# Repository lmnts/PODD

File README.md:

# Post Occupancy Data Device

*A tool to understand how buildings perform in terms of occupant comfort.*

*&nbsp;&nbsp;&nbsp;&nbsp;https://lmnarchitects.com/tech-studio/*

The Post Occupancy Data Device (PODD) is a small, networked, multi-sensor device that:

  * addresses the need for more granular data on buildings once they have been occupied
  * offers a lower cost, less precious alternative to standard building enviornmental sensors
  * gives building designers greater control over the tools available to them to understand their buildings
 
PODD is under active development and should be thought of as early alpha quality for both the software and hardware.

- [Features](#features)
- [Hardware](#hardware)
  - [Operational Hardware](#operational-hardware)
  - [Sensors](#sensors)
- [Building](#building)
  - [Hardware Setup](#hardware-setup)
  - [Software Setup](#software-setup)
- [Data Access](#data-access)
- [Known Issues](#known-issues)
- [License](#license)
- [Reporting Issues](#reporting-issues)
- [Contact](#contact)

## Features

The PODD is our solution to the gap in the available post-occupancy evaluation tools. The units are designed to be networked together in large numbers, storing and uploading data from seven sensors that have been identified as most relevant for occupant comfort in buildings.

Each unit has the following features:

  * Air quality sensors: particulate matter (PM2.5 and PM10), CO<sub>2</sub>, CO
  * Thermal comfort sensors: combined temperature and humidity sensor, radiant temperature
  * Illuminance sensor
  * Sound level sensor
  * On board data storage: micro SD card
  * Real Time Clock (RTC)
  * Wireless communication using 802.15.4 standard (900 MHz)
  * Onboard Ethernet 
  * Power via battery, USB, or PoE
  * Current cost: ~$400 (note: the CO and CO<sub>2</sub> sensors together are 1/4 of the cost and the production cost for the board is currently in the small-batch range)

## Hardware

Details can be found in [Hardware](Hardware).

The PODD is designed to be a self-powered unit that can communicate with other units as well as transmit information over ethernet. The portable battery currently used is the primary source of power. All other power sources provide power by charging the battery. Depending on sample rates, the units can run on battery power for up to 8 days.

### Operational Hardware

The current version of PODD uses the following components to run:

  * Teensy++ 2.0
  * MicroSD Reader 
  * DS3234 Real Time Clock
  * Ethernet Module (for server or other remote communication)
  * PoE module
  * XBee 900 Mesh Kit
  * Rechargeable USB battery
  * Various supporting components (resistors, capacitors, op-amps, etc.)

### Sensors

The current version of PODD uses the following sensors:

  * Sensirion SPS30: particulate matter
  * COZIR-A: CO<sub>2</sub>
  * SPEC Sensor 3SP_CO_1000: CO
  * Honeywell HIH8120-021: dry bulb temperature and humidity
  * PR222J2: radiant temperature
  * OPT3001: illuminance
  * CMR-2747PB-A: sound level

## Building

### Hardware Setup

The PODD can be built entirely on a breadboard for initial prototyping and testing. All parts can be obtained in a DIP package for breadboarding or soldering to a perf-board. For use with the PCB design included, you will need to obtain the supporting components in their SMD packages. The gerber files in the Hardware folder can be used for making the PCB or having it manufactured.

A full list of parts can be found in [this spreadsheet](Hardware/PODD_v1.2_PartsList.xlsx).

To assemble the PODD, see [this assembly document](Hardware/PODD_v1.2_Assembly.pdf).  This document also describes issues with various sensors and other components, and how to operate the sensors.

### Software Setup

You will need the following:

  * [Arduino IDE](https://www.arduino.cc/en/Main/Software)
  * [Teensy add-ons](https://www.pjrc.com/teensy/td_download.html)
  * The sensor and component-specific libraries included in [Libraries](Software/Libraries)

After installing the Arduino IDE and the Teensy add-ons, follow the instructions to [install Arduino Libraries](https://www.arduino.cc/en/Guide/Libraries).

Once the above software is installed, the PODD firmware in [SensorPod_FW](Software/Sketches/SensorPod_FW) can be uploaded to the PODD.  The firmware provides an interactive menu which can be accessed through a serial interface such as provided by the Arduino IDE.  The interactive menu can only be accessed during the PODD startup sequence -- once the PODD enters data-taking mode, it will no longer respond to serial input.

## Data Access
_work in progress_

The PODD collects data from all the sensors at the specified sample rates and logs those to the on-board SD card in the form of a CSV file. All settings are also stored on the SD card as a separate CSV file. If any unit is designated as a controller and connected to Ethernet, the data from all the units on the same network will be uploaded to a server specified by the user.

## Known Issues
_work in progress_

1. Most portable USB power banks automatically shut off to save power whenever the current draw is low: as the PODD draws a much smaller amount of power than the cell phones these power banks are designed to charge, these batteries will often not provide continuous power to a PODD and cannot be used.  The TalentCell batteries we use do not have this feature, but also cannot be recharged via USB/PoE as intended in the current PCB design.
1. R11, which is part of the battery charging circuit, should be 390 Ohms.  The PCB design called for a larger (too large) resistor.
1. The CO sensor output is uncalibrated and we are as yet unsure how to quantify the results.  The C and R pins many be reversed on this sensor's PCB headers.
1. The sound sensor currently provides time-averaged sound levels in an arbitrary linear unit, rather than the logarithmic decibel (dB) scale.  Conversion to dB(Z) is being investigated, but the frequency-weighted dB(A) or dB(C) more commonly used for human hearing may require processing capabilities beyond that provided by the current hardware.

## License

**PODD hardware is released under [Creative Commons Share-alike Non-Commercial 4.0 International](https://creativecommons.org/licenses/by-nc-sa/4.0/).**

**PODD code, firmware, and software is released under the [GNU Affero General Public License](https://www.gnu.org/licenses/).**

See the full text files for details on both licenses.

Our open source goals include 1) sharing new ways to understand buildings with the AEC industry and 2) engaging with a larger group of practitioners and researchers to develop new tools for the AEC industry.

## Reporting Issues

You can open a ticket on [GitHub](https://github.com/lmnts/PODD/issues).

## Contact

Contact pmilusheva@lmnarchitects.com or csavage@lmnarchitects.com with any questions or comments.

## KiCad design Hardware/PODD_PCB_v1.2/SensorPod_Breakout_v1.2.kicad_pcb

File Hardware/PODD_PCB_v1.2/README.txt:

# Assembly

## Teensy++ 2.0 Modifications

The Teensy++ 2.0 is used in 3.3V mode in order to save power. Before plugging the teensy in, please do the following:

# Using these files

The files in this repo are for the LMN SensorPod Phase 1 hardware. To open them, you'll need KiCAD:

- http://kicad-pcb.org/

It may also be helpful to use these libraries:

- https://github.com/mogar/KiCAD_libs

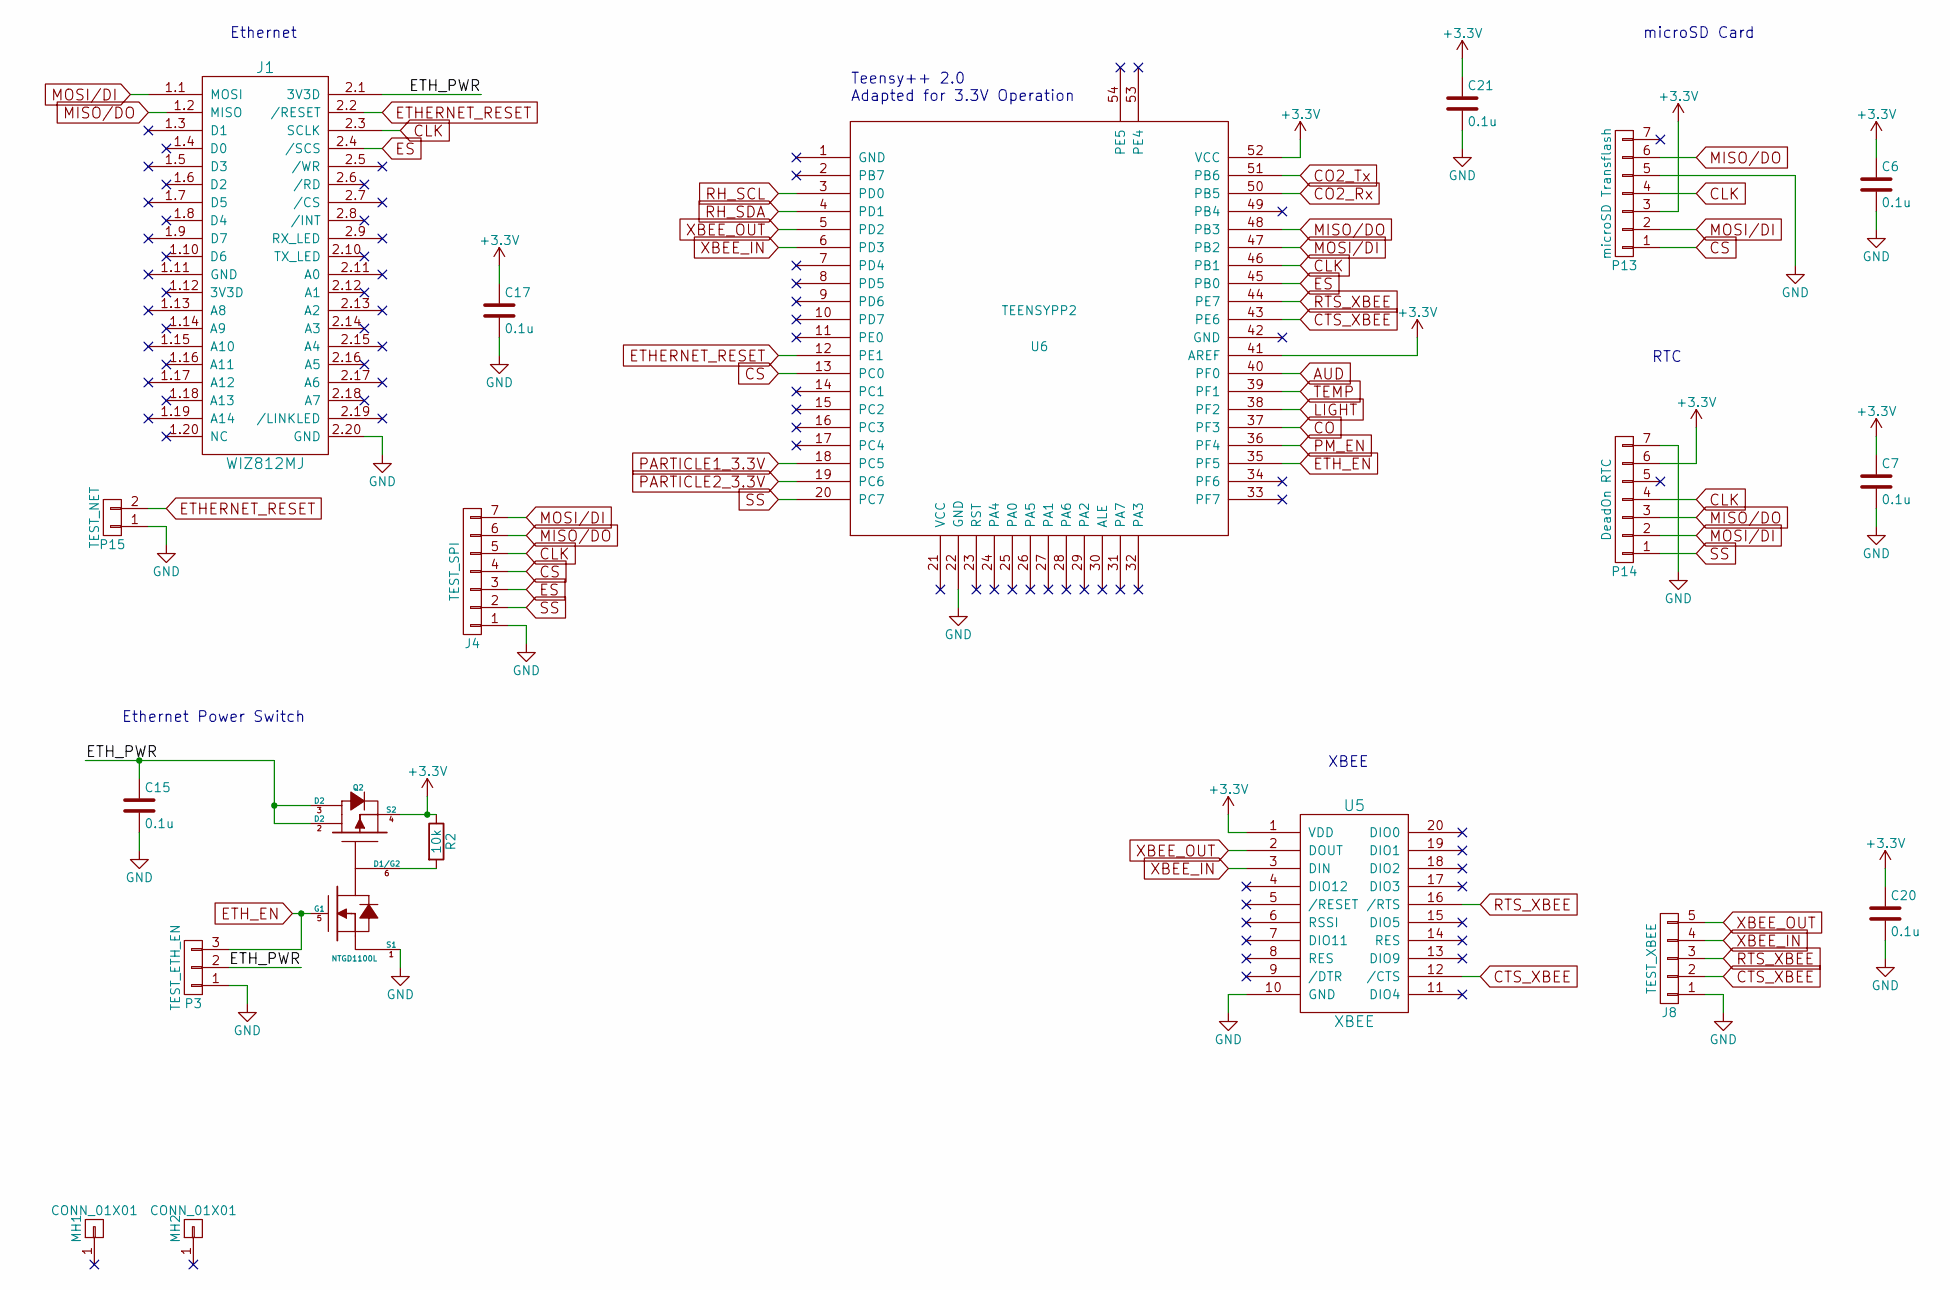
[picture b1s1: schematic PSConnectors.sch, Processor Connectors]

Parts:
C6, C7, C15, C17, C20, C21: 0.1u; C_0805
J1: WIZ812MJ
J4: TEST_SPI; Pin_Header_Straight_1x07_Pitch2.54mm
J8: TEST_XBEE; Pin_Header_Straight_1x05_Pitch2.54mm
MH1, MH2: CONN_01X01; MountingHole_3.2mm_M3
P3: TEST_ETH_EN; Pin_Header_Straight_1x03_Pitch2.54mm
P13: microSD Transflash; SD_Card
P14: DeadOn RTC; DeadOn_RTC
P15: TEST_NET; Pin_Header_Straight_1x02_Pitch2.54mm
Q2: NTGD1100L; TSOT-23-6_HandSoldering
R2: 10k; R_0805
U5: XBEE
U6: TEENSYPP2

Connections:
+3V3: C6.1, C7.1, C17.1, C20.1, C21.1, P13.3, P14.6, Q2.4 (S2), R2.1, U5.1 (VDD), U6.41 (AREF), U6.52 (VCC); also elsewhere on the board
/Processor Connectors/ETH_PWR: C15.1, J1.2.1 (3V3D), P3.2, Q2.2 (D2), Q2.3 (D2)
AUD: U6.40 (PF0); also elsewhere on the board
CLK: J1.2.3 (SCLK), J4.5, P13.4, P14.4, U6.46 (PB1)
CO: U6.37 (PF3); also elsewhere on the board
CO2_Rx: U6.50 (PB5); also elsewhere on the board
CO2_Tx: U6.51 (PB6); also elsewhere on the board
CS: J4.4, P13.1, U6.13 (PC0)
CTS_XBEE: J8.2, U5.12 (/CTS), U6.43 (PE6)
ES: J1.2.4 (/SCS), J4.3, U6.45 (PB0)
ETHERNET_RESET: J1.2.2 (/RESET), P15.2, U6.12 (PE1)
ETH_EN: P3.3, Q2.5 (G1), U6.35 (PF5)
GND: C6.2, C7.2, C15.2, C17.2, C20.2, C21.2, J1.2.20 (GND), J4.1, J8.1, P3.1, P13.5, P14.7, P15.1, Q2.1 (S1), U5.10 (GND), U6.22 (GND); also elsewhere on the board
LIGHT: U6.38 (PF2); also elsewhere on the board
MISO/DO: J1.1.2 (MISO), J4.6, P13.6, P14.3, U6.48 (PB3)
MOSI/DI: J1.1.1 (MOSI), J4.7, P13.2, P14.2, U6.47 (PB2)
unnamed: Q2.6 (D1/G2), R2.2
PARTICLE1_3.3V: U6.18 (PC5); also elsewhere on the board
PARTICLE2_3.3V: U6.19 (PC6); also elsewhere on the board
PM_EN: U6.36 (PF4); also elsewhere on the board
RH_SCL: U6.3 (PD0); also elsewhere on the board
RH_SDA: U6.4 (PD1); also elsewhere on the board
RTS_XBEE: J8.3, U5.16 (/RTS), U6.44 (PE7)
SS: J4.2, P14.1, U6.20 (PC7)
TEMP: U6.39 (PF1); also elsewhere on the board
XBEE_IN: J8.4, U5.3 (DIN), U6.6 (PD3)
XBEE_OUT: J8.5, U5.2 (DOUT), U6.5 (PD2)

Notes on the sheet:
RTC
microSD Card
Ethernet
XBEE
Teensy++ 2.0 Adapted for 3.3V Operation
Ethernet Power Switch

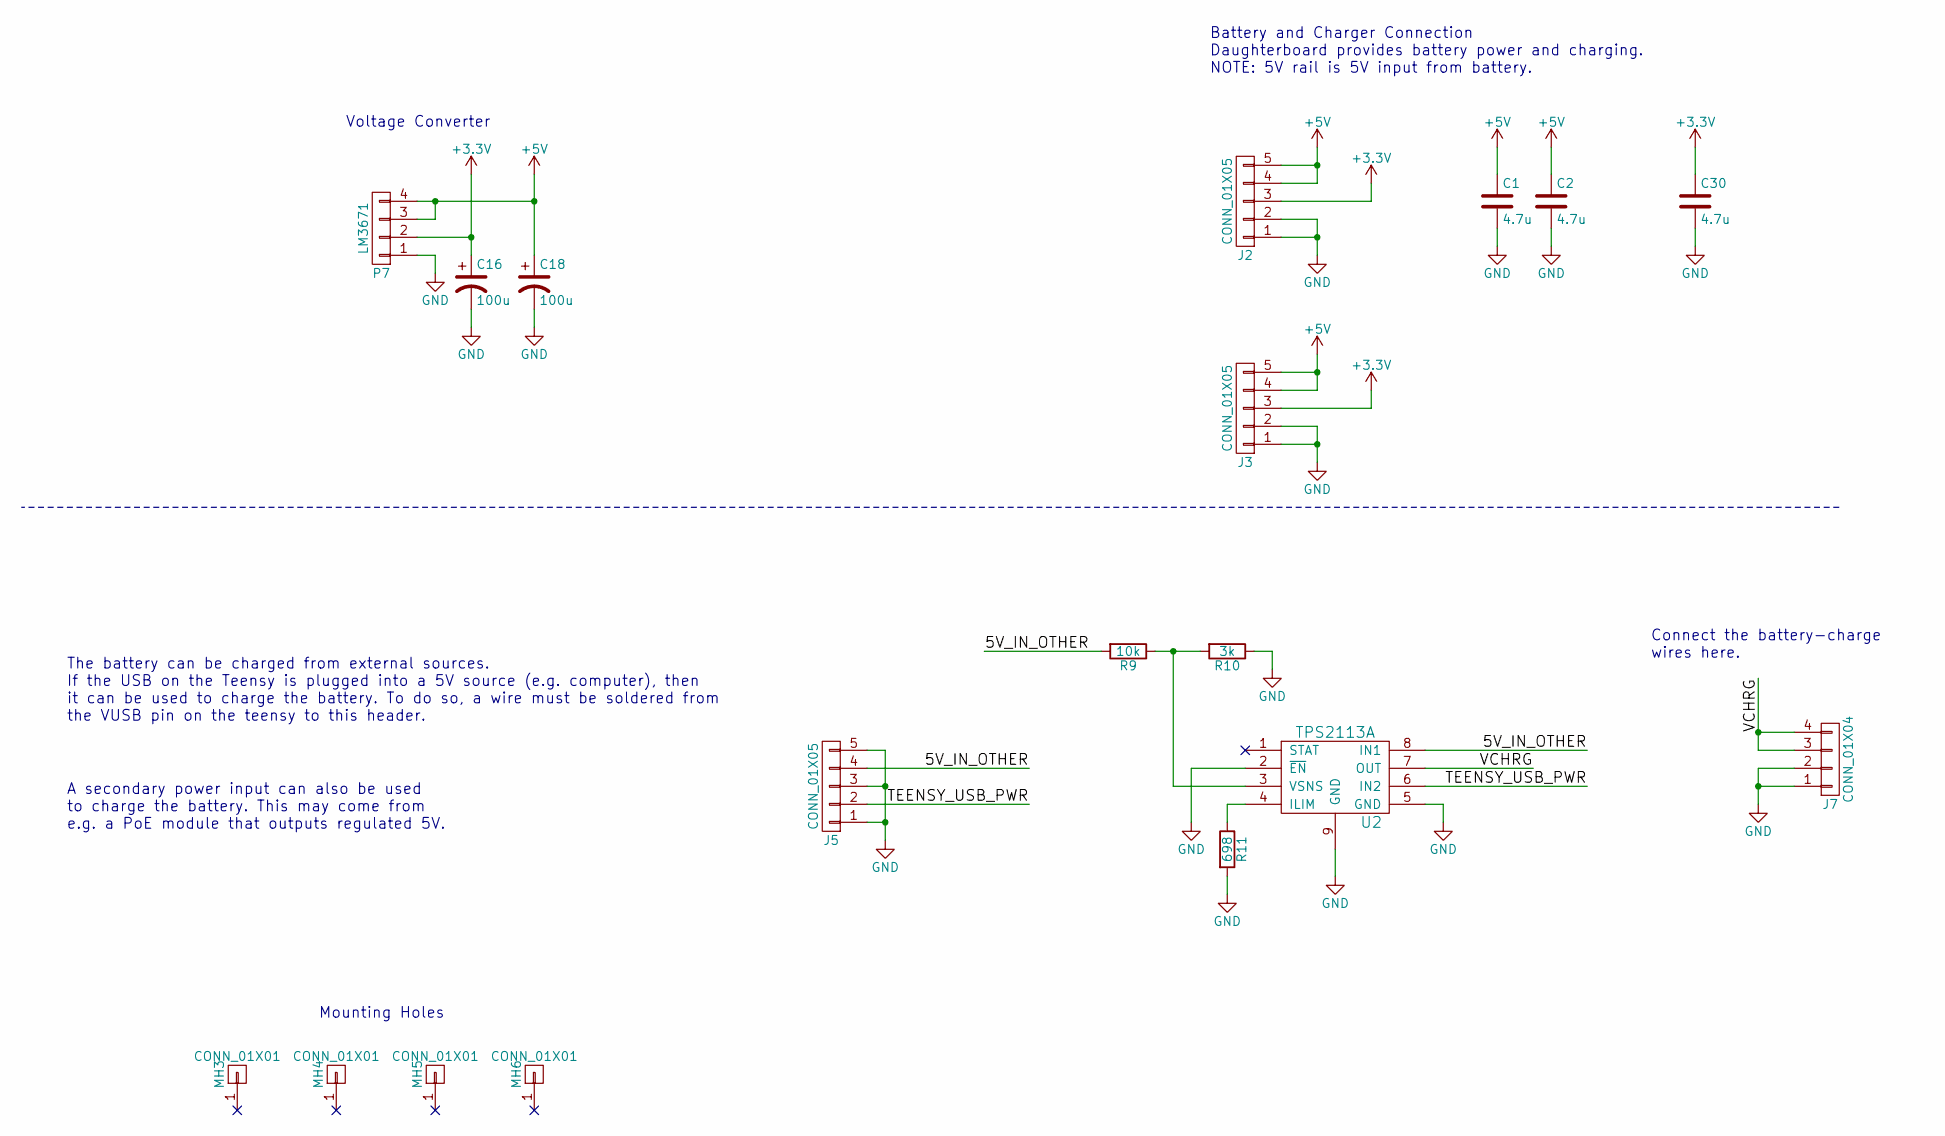
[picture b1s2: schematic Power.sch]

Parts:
C1, C2, C30: 4.7u; C_0805
C16, C18: 100u; CP_Radial_D5.0mm_P2.00mm
J2, J3: CONN_01X05; Pin_Header_Straight_1x05
J5: CONN_01X05; Pin_Header_Straight_1x05_Pitch2.54mm
J7: CONN_01X04; Pin_Header_Straight_1x04_Pitch2.54mm
MH3, MH4, MH5, MH6: CONN_01X01; MountingHole_3.2mm_M3
P7: LM3671
R9: 10k; R_0805
R10: 3k; R_0805
R11: 698; R_0805
U2: TPS2113A; SON-8

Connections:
+3V3: C16.1, C30.1, J2.3, J3.3, P7.2; also elsewhere on the board
+5V: C1.1, C2.1, C18.1, J2.4, J2.5, J3.4, J3.5, P7.3, P7.4; also elsewhere on the board
/Power/5V_IN_OTHER: J5.4, R9.2, U2.8 (IN1)
/Power/TEENSY_USB_PWR: J5.2, U2.6 (IN2)
/Power/VCHRG: J7.3, J7.4, U2.7 (OUT)
GND: C1.2, C2.2, C16.2, C18.2, C30.2, J2.1, J2.2, J3.1, J3.2, J5.1, J5.3, J5.5, J7.1, J7.2, P7.1, R10.1, R11.2, U2.2 (~EN), U2.5 (GND), U2.9 (GND); also elsewhere on the board
unnamed: R9.1, R10.2, U2.3 (VSNS)
unnamed: R11.1, U2.4 (ILIM)

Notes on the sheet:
Mounting Holes
Battery and Charger Connection Daughterboard provides battery power and charging. NOTE: 5V rail is 5V input from battery.
Voltage Converter
The battery can be charged from external sources. If the USB on the Teensy is plugged into a 5V source (e.g. computer), then it can be used to charge the battery. To do so, a wire must be soldered from the VUSB pin on the teensy to this header.
A secondary power input can also be used to charge the battery. This may come from e.g. a PoE module that outputs regulated 5V.
Connect the battery-charge wires here.

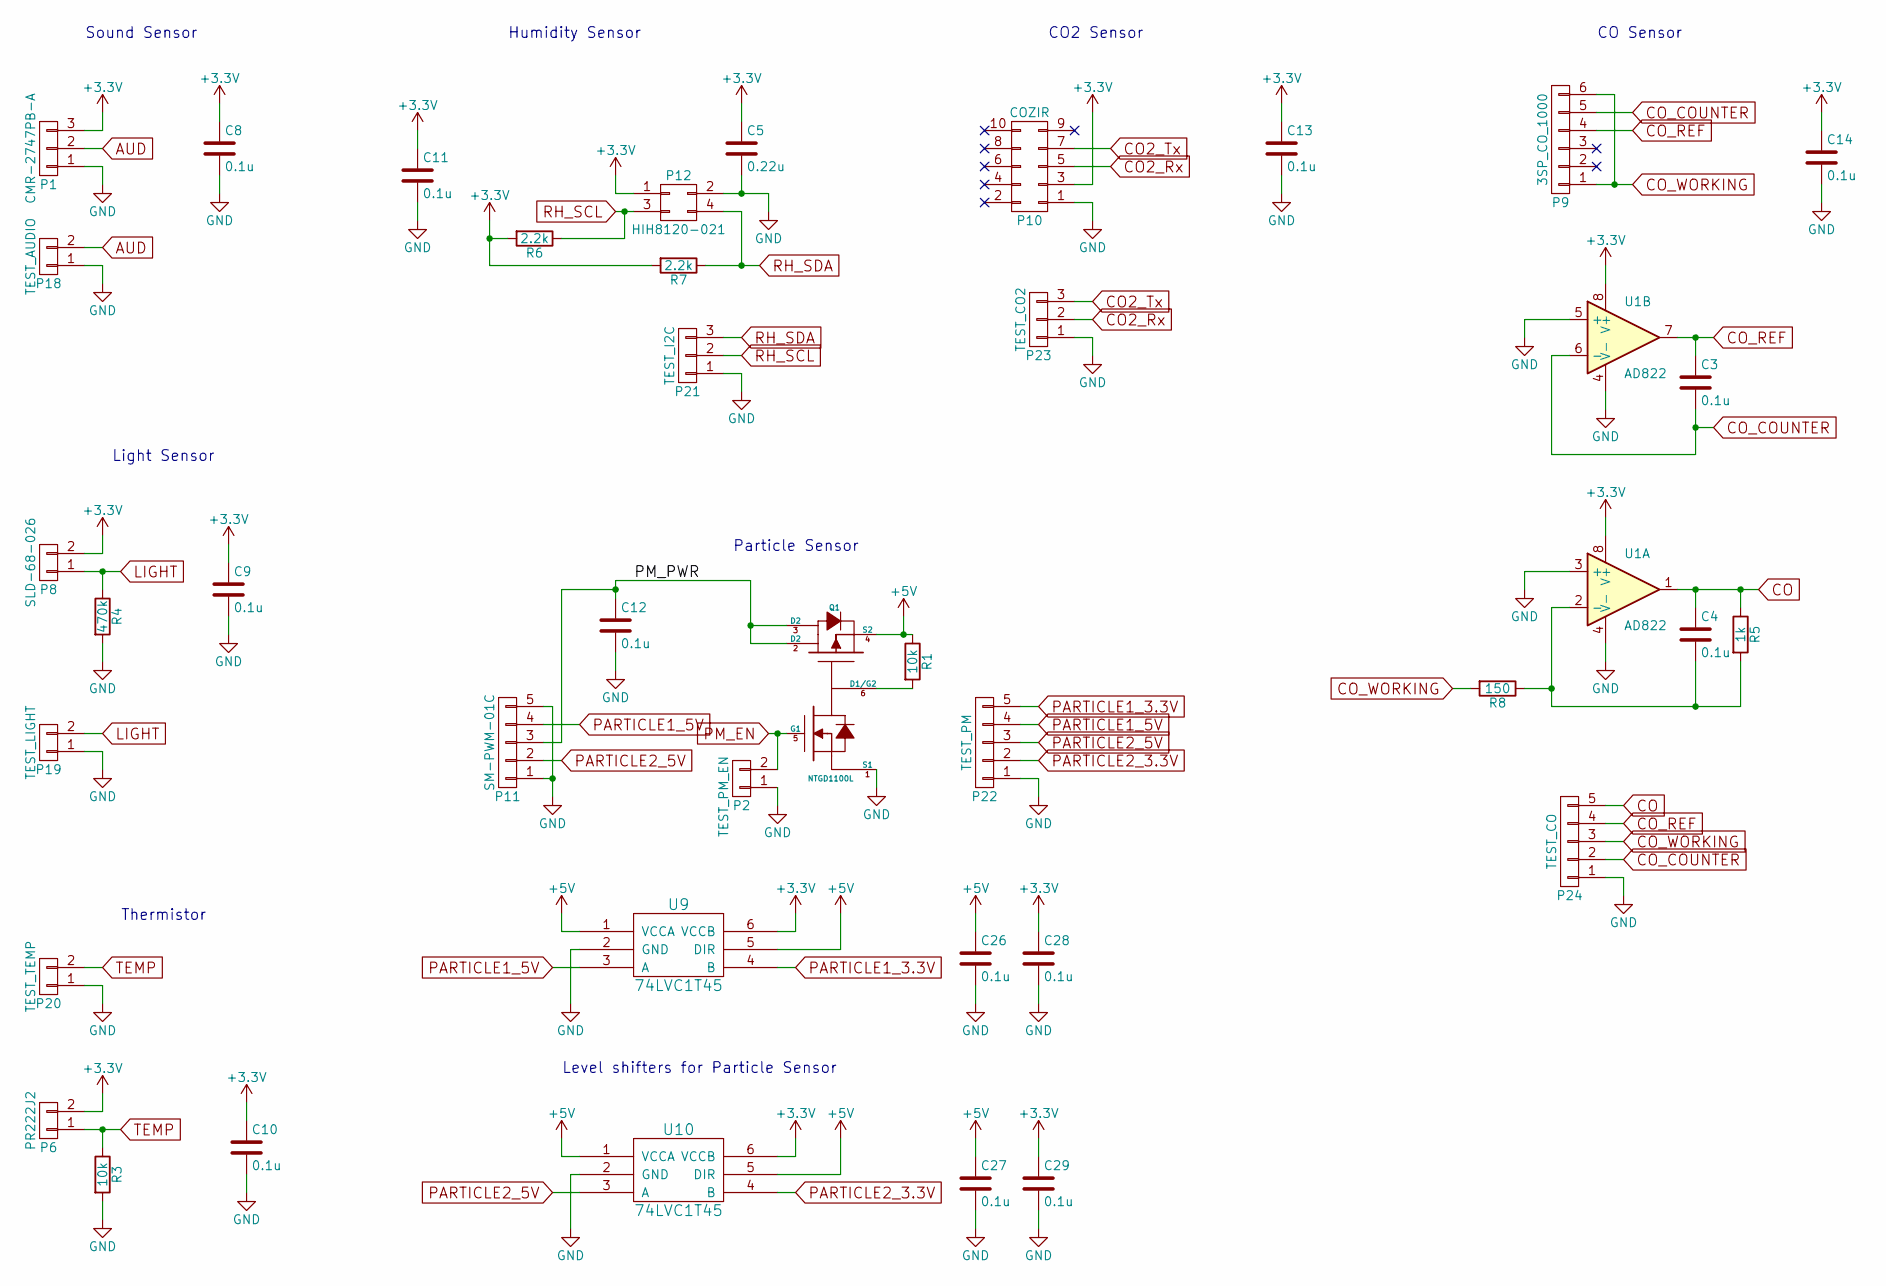
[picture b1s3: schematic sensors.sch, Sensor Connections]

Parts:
C3, C4, C8, C9, C10, C11, C12, C13, C14, C26, C27, C28, C29: 0.1u; C_0805
C5: 0.22u; C_0805
P1: CMR-2747PB-A
P2: TEST_PM_EN; Pin_Header_Straight_1x02_Pitch2.54mm
P6: PR222J2; R_Axial_DIN0204_L3.6mm_D1.6mm_P2.54mm_Vertical
P8: SLD-68-026
P9: 3SP_CO_1000
P10: COZIR
P11: SM-PWM-01C
P12: HIH8120-021
P18: TEST_AUDIO; Pin_Header_Straight_1x02_Pitch2.54mm
P19: TEST_LIGHT; Pin_Header_Straight_1x02_Pitch2.54mm
P20: TEST_TEMP; Pin_Header_Straight_1x02_Pitch2.54mm
P21: TEST_I2C; Pin_Header_Straight_1x03_Pitch2.54mm
P22: TEST_PM; Pin_Header_Straight_1x05_Pitch2.54mm
P23: TEST_CO2; Pin_Header_Straight_1x03_Pitch2.54mm
P24: TEST_CO; Pin_Header_Straight_1x05_Pitch2.54mm
Q1: NTGD1100L; TSOT-23-6_HandSoldering
R1, R3: 10k; R_0805
R4: 470k; R_0805
R5: 1k; R_0805
R6, R7: 2.2k; R_0805
R8: 150; R_0805
U1: AD822; DIP-8_W7.62mm
U9, U10: 74LVC1T45; SOT-23-6

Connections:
+3V3: C5.1, C8.1, C9.1, C10.1, C11.1, C13.1, C14.1, C28.1, C29.1, P1.3, P6.2, P8.2, P10.3, P12.1, R6.2, R7.2, U1.8 (V+), U9.6 (VCCB), U10.6 (VCCB); also elsewhere on the board
+5V: C26.1, C27.1, Q1.4 (S2), R1.1, U9.1 (VCCA), U9.5 (DIR), U10.1 (VCCA), U10.5 (DIR); also elsewhere on the board
/Sensors/PM_PWR: C12.1, P11.3, Q1.2 (D2), Q1.3 (D2)
AUD: P1.2, P18.2; also elsewhere on the board
CO: C4.1, P24.5, R5.1, U1.1; also elsewhere on the board
CO2_Rx: P10.5, P23.2; also elsewhere on the board
CO2_Tx: P10.7, P23.3; also elsewhere on the board
CO_COUNTER: C3.2, P9.5, P24.2, U1.6 (-)
CO_REF: C3.1, P9.4, P24.4, U1.7
CO_WORKING: P9.1, P9.6, P24.3, R8.2
GND: C5.2, C8.2, C9.2, C10.2, C11.2, C12.2, C13.2, C14.2, C26.2, C27.2, C28.2, C29.2, P1.1, P2.1, P10.1, P11.1, P11.5, P12.2, P18.1, P19.1, P20.1, P21.1, P22.1, P23.1, P24.1, Q1.1 (S1), R3.2, R4.2, U1.3 (+), U1.4 (V-), U1.5 (+), U9.2 (GND), U10.2 (GND); also elsewhere on the board
LIGHT: P8.1, P19.2, R4.1; also elsewhere on the board
unnamed: C4.2, R5.2, R8.1, U1.2 (-)
unnamed: Q1.6 (D1/G2), R1.2
PARTICLE1_3.3V: P22.5, U9.4 (B); also elsewhere on the board
PARTICLE1_5V: P11.4, P22.4, U9.3 (A)
PARTICLE2_3.3V: P22.2, U10.4 (B); also elsewhere on the board
PARTICLE2_5V: P11.2, P22.3, U10.3 (A)
PM_EN: P2.2, Q1.5 (G1); also elsewhere on the board
RH_SCL: P12.3, P21.2, R6.1; also elsewhere on the board
RH_SDA: P12.4, P21.3, R7.1; also elsewhere on the board
TEMP: P6.1, P20.2, R3.1; also elsewhere on the board

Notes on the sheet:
Sound Sensor
Light Sensor
Thermistor
Particle Sensor
CO2 Sensor
Humidity Sensor
CO Sensor
Level shifters for Particle Sensor

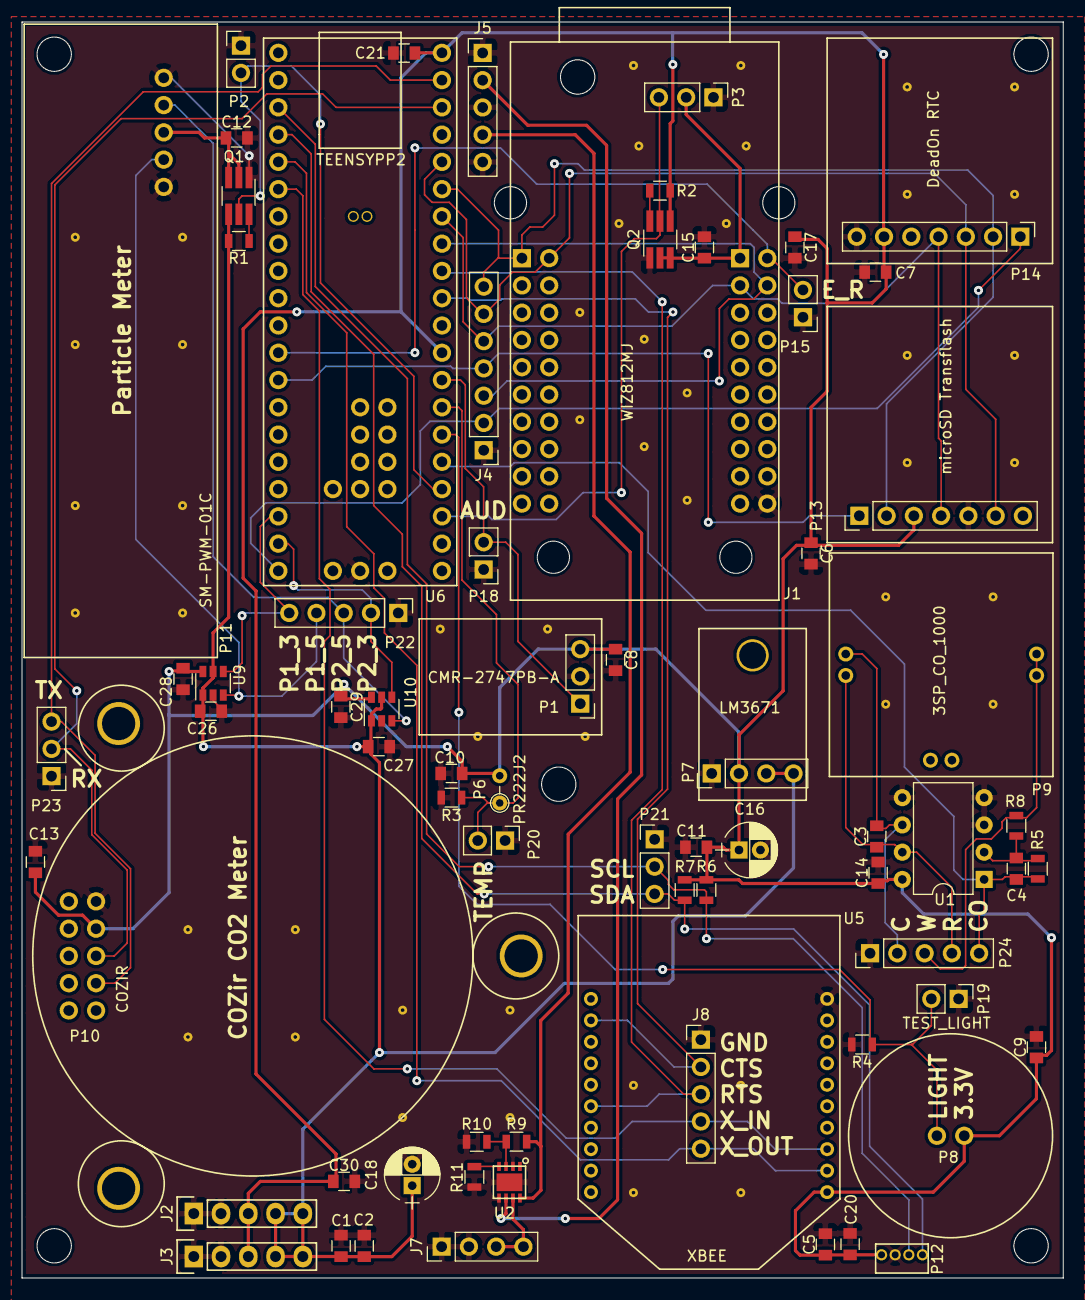
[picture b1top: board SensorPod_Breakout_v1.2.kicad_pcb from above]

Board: 2 copper layers, 97.0 x 117.0 mm, 77 parts (0 on the bottom side), 41 nets.

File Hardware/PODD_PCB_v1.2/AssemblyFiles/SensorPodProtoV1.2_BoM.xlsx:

Id | Designator | Package | Quantity | Designation | Supplier | Supplier Part Number
1 | P6 | R_Axial_DIN0204_L3.6mm_D1.6mm_P2.54mm_Vertical | 1 | PR222J2 | DigiKey | 615-1068-ND
2 | U9,U10 | SOT-23-6 | 2 | 74LVC1T45 | DigiKey | 296-30381-1-ND
3 | U1 | DIP-8_W7.62mm | 1 | AD822 | DigiKey | AD822ANZ-ND
4 | R1,R2,R3,R9 | R_0805 | 4 | 10k | DigiKey | 311-10.0KCRCT-ND
5 | J1 | WIZ812MJ | 1 | WIZ812MJ | DigiKey | 1278-1010-ND
6 | P1 | CMR-2747PB-A | 1 | CMR-2747PB-A | SparkFun | BOB-12758
7 | P8 | SLD-68-026 | 1 | SLD-68-026 | DigiKey | SLD-68-026-ND
8 | P9 | 3SP_CO_1000 | 1 | 3SP_CO_1000 | DigiKey | 1684-1000-ND
9 | P10 | COZIR | 1 | COZIR | CO2Meter.com | COZIR-AV-1
10 | P12 | HIH8120-021 | 1 | HIH8120-021 | DigiKey | 480-5706-1-ND
11 | P13 | SD_Card | 1 | microSD Transflash | SparkFun | BOB-00544
12 | P14 | DeadOn_RTC | 1 | DeadOn RTC | SparkFun | BOB-10160
13 | U5 | XBEE | 1 | XBee Pro 9B-DMWT | DigiKey | 602-1301-ND
14 | P11 | SM-PWM-01C | 1 | SM-PWM-01C | DigiKey | 235-1443-ND
15 | P7 | LM3671 | 1 | LM3671 | AdaFruit | 2745
16 | U6 | TEENSYPP2 | 1 | TEENSYPP2 | DigiKey | 1568-1232-ND
17 | U2 | SON-8 | 1 | TPS2113A | DigiKey | 296-46373-1-ND
18 | Q1,Q2 | TSOT-23-6_HandSoldering | 2 | NTGD1100L | DigiKey | NTGD1100LT1GOSCT-ND
19 | C1,C2,C30 | C_0805 | 3 | 4.7u | DigiKey | 1276-3022-1-ND
20 | C3,C4,C6,C7,C8,C9,C10,C11,C12,C13,C14,C15,C17,C20,C21,C26,C27,C28,C29 | C_0805 | 19 | 0.1u | DigiKey | 399-1170-1-ND
21 | C5 | C_0805 | 1 | 0.22u | DigiKey | 1276-6496-1-ND
22 | R4 | R_0805 | 1 | 470k | DigiKey | RMCF0805JT470KCT-ND
23 | R5 | R_0805 | 1 | 1k | DigiKey | 311-1.0KARCT-ND
24 | R6,R7 | R_0805 | 2 | 2.2k | DigiKey | RMCF0805JT2K20CT-ND
25 | R8 | R_0805 | 1 | 150 | DigiKey | RMCF0805JT150RCT-ND
26 | R10 | R_0805 | 1 | 3k | DigiKey | RMCF0805JT3K00CT-ND
27 | R11 | R_0805 | 1 | 698 | DigiKey | 311-698CRCT-ND
28 | C16,C18 | CP_Radial_D5.0mm_P2.00mm | 2 | 100u | DigiKey | 732-8598-1-ND
29 |  | XBEE |  | XBee Headers | AdaFruit | 366
30 |  | Female Headers |  | Female Headers | AdaFruit | 598
31 |  | Male Headers |  | Male Headers | AdaFruit | 2671

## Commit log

2018-04-16 Adding correct resistor value for R11 to Readme
2018-06-27 adding Sample Data folder to repository
2018-06-27 adding the settings files to the Sample Data folder
2018-08-09 Address compiler warnings and improve sensor read timing in the Cozir library.
2018-08-09 Remove unused libraries.
2018-08-09 Revert locally modified library ManyAlarms to upstream TimeAlarms (modifications can be achieved through a preprocessor flag instead); update to current version of TimeAlarms [1.5.0].
2018-08-09 Replaced HIH61XX library (by Tomas Van Verrewegen) by HIH61xx library (by Steve Marple) as the latter is available in the Arduino library repository.
2018-08-09 Remove unused SoftWire library and unnecessary reference.
2018-08-10 Added README to libraries directory.
2018-08-10 Revert SparkFun DS 3234 library name to upstream name.
2018-08-10 Add const qualifiers to various char* arguments to address deprecated string conversions.
2018-08-20 Added network debugging output and automatic reconnection logic.
2018-08-21 Replacement of photodiode sensor with OPT3001 ambient light sensor; added corresponding ClosedCube Arduino library. Added OPT3001 testing sketch. Fixed several HIH8120-related bugs. Added pod_util.{h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
2018-08-21 Added debug output option for drones.
2018-09-11 Improvements to serial interface performance (notably, substantially reducing errors and data corruption) via changing serial interface implementations & usage, and altering main thread & interrupt s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
2018-09-12 Alterations to XBee packetization and buffering for improved performance and better handling of missing packet data (buffer overflows). Routines should now recognize when packet data is lost and igno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
2018-09-13 Split XBee startup into separate initialization and start-serial-monitoring routines. Remove unnecessary XBee serial monitoring (for incoming packets) from drones.
2018-09-14 Modified TimeAlarms library to increase the maximum number of timers (used for sensor measurements).
2018-09-18 Added routines for SM-PWM-01C particulate matter (PM) sensor that can use ISRs to read the sensor instead of holding the main thread for extended periods. Improved conversion of PM sensor readings to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
2018-09-18 Clean up particulate matter sensor (SM-PWM-01C) documentation; add own plots to documentation.
2018-09-19 Added additional tracking information in routines for SM-PWM-01C particulate matter (PM) sensor, for the purpose of identifying performance and calibration (work in progress).
2018-09-20 Debugging statements for SD card testing.
2018-09-20 Remove debugging statements.
2018-09-20 More/cleaner serial messaging on startup. Output of compilation info on startup.
2018-09-21 Added particulate matter sensor testing routines.
2018-09-21 Fix particular matter sensor moving average calculation bug.
2018-09-21 Improved particular matter moving average calculations.
2018-09-24 Updating and reorganization of hardware data sheets.
2018-09-25 Remove spurious backup files. Add PCB power traces images.
2018-09-25 Moved compilation info output to own routine. Added Teensyduino version to compilation info output.
2019-04-04 Add data sheet for Sensirion SPS30 particulate matter sensor.
2019-04-04 Add Arduino library for Sensirion SPS30 particulate matter sensor.
2019-04-09 Bug fix in sps30 library: stop routine was sending start command.
2019-04-09 Added Sensirion SPS30 particulate matter sensor routines. Required CO2 sensor serial interface be changed from NeoSWSerial to SoftwareSerial. SPS30's required baud rate (115200) seems to be higher th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
2019-04-11 Remove usage of particulate matter sensor routines until hardware can be connected (cannot use serial or I2C through PCB's one-way voltage level translators). Revert CO2 sensor serial interface to Ne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
2019-04-11 Change SPS30 access to I2C bus, via shared humidity/thermometer/optical sensor I2C pins (SPS30 SCL and SDA lines operate fine on 3V I2C bus).
2019-04-11 Removed debug statement. F()'ed some strings.
2019-04-19 New interactive menu system on startup.
2019-04-19 Replace external CozIR CO2 sensor library with internal code.
2019-04-19 More robust CozIR CO2 sensor serial interactions.
2019-04-24 Redesign sound measurements to occur within an ISR to avoid tying up CPU for extended periods. Sound level is now based on the standard deviation of the samples, which provides a better metric of the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
2019-04-25 New/updated routines for various sensors to allow for communication testing and to improve code modularity. Communication with HIH8120 temperature/humidity sensor implemented entirely in firmware, re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
2019-04-29 Change invalid sound level value to NAN. Add sound level validity check to sound logging. Change testing routines' number of cycles argument to long (int could run out in less than a day at 1 second 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
2019-04-29 Improved loop handling in sensor testing routines.
2019-04-29 Removed no longer needed cozir and HIH61xx Arduino libraries. Added TimerThree library, used by sound sampling routines. Updated other timing libraries to current versions.
2019-04-30 Added sensor testing routine. Redid sensor initialization and startup. Improved handling of string constants (reduced memory usage).
2019-04-30 Moved generic serial-related routines into separate pod_serial.h/cpp files.
2019-05-01 Pulled all interactive menu related code into pod_menu.h/cpp files. Created sensor menu for configuring/testing the sensors.
2019-05-13 Removed unused sps30 library. Updated libraries README.
2019-05-15 Added new clock time management system: RTC stores UTC and local time is determined from a configurable timezone setting (including adjustments for daylight saving time). Unix timestamp is now core t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
2019-05-16 Add packet length to XBee transmissions for error checking. Changed SD log file naming (now date based).
2019-05-16 Moved define statements from networking header file to cpp file. Changed date/time output format and added unix timestamp to SD data log files. Fixed typos.
2019-05-17 Removed no longer used SparkFun DS3234 library. Removed no longer needed CO2 calibration sketch. Database uploads using http POST now wait for server to respond before closing the connection as serve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
2019-05-20 Fixed off-by-one index bug in XBee buffer.
2019-05-20 Limit number of XBee packets processed per loop to avoid case where XBee packets arrive faster than can be uploaded to database server, preventing main loop from cycling. Added valid IP check to netw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
2019-05-21 Remove deprecated/unused code. Streamlined network connection checking.
2019-05-21 Removed unused AsyncDelay library. Added Timezone library files.
2019-05-21 Added delays and network calls to work around a network socket resource leak issue. Moved opening of incoming UDP socket to only within the NTP request routine, the only place it is used (was previou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
2019-05-22 Increased minimum network reconnection interval to 60 seconds. Added missing ethernet reconnection flagging in ethernet setup routine.
2019-05-23 Increased XBee buffer size to reduce incidents of buffer overflows. Additional OPT3001 light sensor commenting. Removed unneeded OPT3001 testing sketch.
2019-05-23 Directory renaming.
2019-05-24 Removed unused sensor documentation.
2019-05-28 Change drone-to-coordinator addressing: coordinator now routinely broadcasts its XBee serial number for drone PODDs to use as XBee network destination address. This works around issue where DigiMesh 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
2019-05-28 Added missing newline on RTC update serial message.
2019-05-29 Fixed menu system typo.
2019-05-29 Added missing sps30 library to Libraries directory. Fixed coordinator address update displaying local XBee serial number on command line instead of new destination. Modified some default configuratio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
2019-05-29 Output if log file is existing or new. Do not write header to existing log file. Do not upload invalid CO2 measurements.
2019-06-03 Reduced I2C timeouts in SPS30 library to avoid unnecessary delays when no SPS30 sensor is attached.
2019-06-04 Disabled serial interface in SPS library to avoid software serial library conflicts.
2019-06-07 Added SPS30 mechanical design guidelines document.
2019-07-01 Updated main readme. Updated parts list. Remove spurious backup file.
2019-07-02 Added missing assembly document.
2019-07-02 Fixed typo in main readme.
2019-08-16 Improved network (re)connection algorithms. Configuration and rates logging moved to later in startup to improve likelihood of valid network connection. Configuration now logged at every startup. Deb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
2019-08-16 Reorder startup sequence: try to obtain network connection earlier.
2019-08-16 Add delay before reading CO2 sensor after calibration to allow sensor to take reading.
2019-08-21 Modified sps30 library to reduce timeout period when no SPS30 is present.
2019-08-21 Added XBee settings to interactive menu. Streamlined XBee settings retrieval and updating.
2019-08-22 Added missing globe temperature presence check in sensor check routine. Sensor check routine now turns on SPS30 power to allow presence of SPS30 to be determined. Added routine to test for presence o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
2019-08-23 Fixed type mismatch in getSerialLong routine.
2019-08-24 Partial implementation and testing of new SPS30 interface routines.
2019-08-24 Internal implementation of I2C routines for communicating with SPS30 particulate matter sensor. Removed no longer needed sps30 library.
2019-08-27 Fixed typo in serial output.
2019-08-29 Added ability to configure static IP address. Static IP parameters saved to EEPROM. Display of additional network parameters. Fixed bug in serial prompts leading to printing of extra newline in some 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
2019-09-25 Added coordinator address broadcast on coordinator start for quicker network updating. Updates to Cozir CO2 sensor routines. Disable CO2 auto-calibration. Repeat CO2 measurement retrieval if it fails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
2019-10-07 Improvements to CozIR serial interface handling. Add ability to recalibrate CO2 sensor using a sensor reading along with the actual CO2 level for that reading. CO2 recalibration in PODD startup menu 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
